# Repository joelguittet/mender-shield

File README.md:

# mender-shield

The Mender Shield illustrates the capability to run a Mender client on heterogeneous platforms such as RaspberryPi (Linux based) and MCUs (RTOS/bare metal).

The following picture shows the Mender devices in the field with the mender-shield on the front, RaspberryPi and ESP32 platforms in the back:
- The Mender logo is displayed on the front of the shield, with an animation of the purple LEDs when an artifact is being downloaded.
- The background color indicates the connectivity status (blue is connected, green is idle, red in case of error).

The following picture shows both sides of the mender-shield:
- The RaspberryPi side has KTD2061 and KTD2058 LEDs drivers from [Kinetic technologies](https://www.kinet-ic.com/ktd2061) driving the 18 RGB LEDs (9 for each side of the PCB) and the [HAT ID EEPROM](https://datasheets.raspberrypi.com/hat/hat-plus-specification.pdf).
- The Arduino side has [ATECC608B](https://www.microchip.com/en-us/product/atecc608b) secure element used to authenticate the device and user EEPROM intented to store [Zephyr LLEXT](https://docs.zephyrproject.org/latest/services/llext/index.html) binary so that the shield also embeds the firmware used to control the display!

[Mender MCU client](https://github.com/joelguittet/mender-mcu-client) is an open source over-the-air (OTA) library updater for MCU devices. Check-out the source and demonstration examples!

## Hardware

The project has been created with [Kicad](https://www.kicad.org/), you can browse the project on [KiCanvas](https://kicanvas.org/?github=https%3A%2F%2Fgithub.com%2Fjoelguittet%2Fmender-shield%2Ftree%2Fmaster%2Fhardware). Gerber files used to manufacture the board are provided.

## Software

The software supports includes a script to perform a very simple demonstration on Raspberry Pi 3 device and an ESP-IDF based application used with the [Wemos D1 r32](.github/docs/Wemos-D1-R32.pdf) ESP32-based evaluation board.

## License

Copyright joelguittet and mender-mcu-client contributors

Licensed under the Apache License, Version 2.0 (the "License");
you may not use this file except in compliance with the License.
You may obtain a copy of the License at

    http://www.apache.org/licenses/LICENSE-2.0

Unless required by applicable law or agreed to in writing, software
distributed under the License is distributed on an "AS IS" BASIS,
WITHOUT WARRANTIES OR CONDITIONS OF ANY KIND, either express or implied.
See the License for the specific language governing permissions and
limitations under the License.

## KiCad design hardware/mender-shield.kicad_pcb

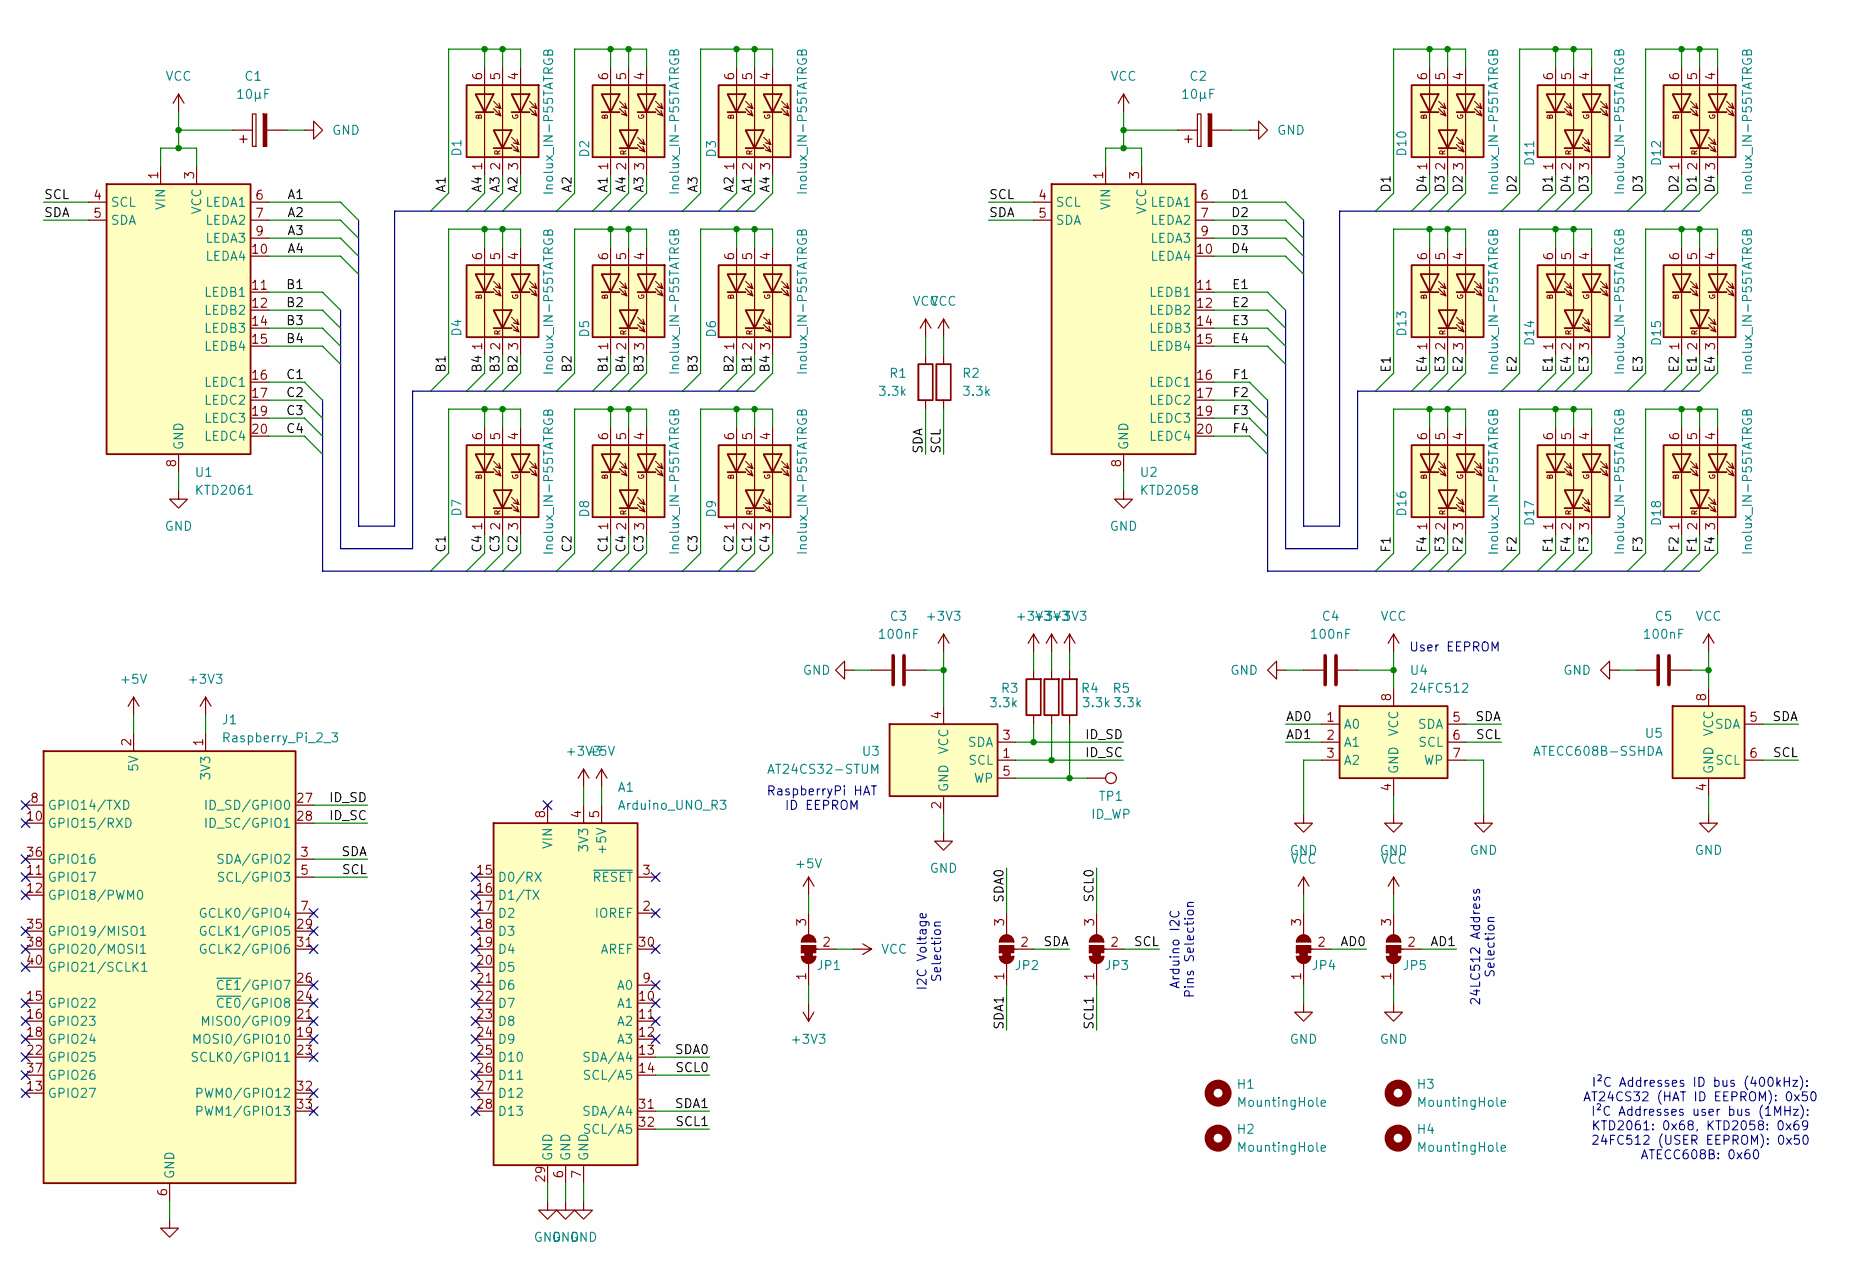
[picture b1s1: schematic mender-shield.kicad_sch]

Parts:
A1: Arduino_UNO_R3
C1, C2: 10µF; C_0805_2012Metric
C3, C4, C5: 100nF; C_0805_2012Metric
D1, D2, D3, D4, D5, D6, D7, D8, D9, D10, D11, D12, D13, D14, D15, D16, D17, D18: Inolux_IN-P55TATRGB; LED_Inolux_IN-P55TATRGB_PLCC6_5.0x5.5mm_P1.8mm
H1, H2, H3, H4: MountingHole; MountingHole_2.7mm_M2.5_DIN965
J1: Raspberry_Pi_2_3; PinSocket_2x20_P2.54mm_Vertical
JP1, JP2, JP3, JP4, JP5: SolderJumper_3_Bridged12; SolderJumper-3_P1.3mm_Bridged12_RoundedPad1.0x1.5mm_NumberL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
R1, R2, R3, R4, R5: 3.3k; R_0805_2012Metric
TP1: ID_WP; TestPoint_Pad_D1.5mm
U1: KTD2061; UQFN-20-1EP_3x3mm_P0.4mm_EP1.7x1.7mm_ThermalVias
U2: KTD2058; UQFN-20-1EP_3x3mm_P0.4mm_EP1.7x1.7mm_ThermalVias
U3: AT24CS32-STUM; SOT-23-5
U4: 24FC512; SOIC-8_3.9x4.9mm_P1.27mm
U5: ATECC608B-SSHDA; SOIC-8_3.9x4.9mm_P1.27mm

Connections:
+3V3: A1.4 (3V3), C3.2, J1.1 (3V3), J1.17 (3V3), JP1.1 (A), R3.2, R4.2, R5.2, U3.4 (VCC)
+5V: A1.5 (+5V), J1.2 (5V), J1.4 (5V), JP1.3 (B)
/A1: D1.4 (AG), D1.5 (AR), D1.6 (AB), D2.1 (KB), D3.2 (KR), U1.6 (LEDA1)
/A2: D1.3 (KG), D2.4 (AG), D2.5 (AR), D2.6 (AB), D3.1 (KB), U1.7 (LEDA2)
/A3: D1.2 (KR), D2.3 (KG), D3.4 (AG), D3.5 (AR), D3.6 (AB), U1.9 (LEDA3)
/A4: D1.1 (KB), D2.2 (KR), D3.3 (KG), U1.10 (LEDA4)
/AD0: JP4.2 (C), U4.1 (A0)
/AD1: JP5.2 (C), U4.2 (A1)
/B1: D4.4 (AG), D4.5 (AR), D4.6 (AB), D5.1 (KB), D6.2 (KR), U1.11 (LEDB1)
/B2: D4.3 (KG), D5.4 (AG), D5.5 (AR), D5.6 (AB), D6.1 (KB), U1.12 (LEDB2)
/B3: D4.2 (KR), D5.3 (KG), D6.4 (AG), D6.5 (AR), D6.6 (AB), U1.14 (LEDB3)
/B4: D4.1 (KB), D5.2 (KR), D6.3 (KG), U1.15 (LEDB4)
/C1: D7.4 (AG), D7.5 (AR), D7.6 (AB), D8.1 (KB), D9.2 (KR), U1.16 (LEDC1)
/C2: D7.3 (KG), D8.4 (AG), D8.5 (AR), D8.6 (AB), D9.1 (KB), U1.17 (LEDC2)
/C3: D7.2 (KR), D8.3 (KG), D9.4 (AG), D9.5 (AR), D9.6 (AB), U1.19 (LEDC3)
/C4: D7.1 (KB), D8.2 (KR), D9.3 (KG), U1.20 (LEDC4)
/D1: D10.4 (AG), D10.5 (AR), D10.6 (AB), D11.1 (KB), D12.2 (KR), U2.6 (LEDA1)
/D2: D10.3 (KG), D11.4 (AG), D11.5 (AR), D11.6 (AB), D12.1 (KB), U2.7 (LEDA2)
/D3: D10.2 (KR), D11.3 (KG), D12.4 (AG), D12.5 (AR), D12.6 (AB), U2.9 (LEDA3)
/D4: D10.1 (KB), D11.2 (KR), D12.3 (KG), U2.10 (LEDA4)
/E1: D13.4 (AG), D13.5 (AR), D13.6 (AB), D14.1 (KB), D15.2 (KR), U2.11 (LEDB1)
/E2: D13.3 (KG), D14.4 (AG), D14.5 (AR), D14.6 (AB), D15.1 (KB), U2.12 (LEDB2)
/E3: D13.2 (KR), D14.3 (KG), D15.4 (AG), D15.5 (AR), D15.6 (AB), U2.14 (LEDB3)
/E4: D13.1 (KB), D14.2 (KR), D15.3 (KG), U2.15 (LEDB4)
/F1: D16.4 (AG), D16.5 (AR), D16.6 (AB), D17.1 (KB), D18.2 (KR), U2.16 (LEDC1)
/F2: D16.3 (KG), D17.4 (AG), D17.5 (AR), D17.6 (AB), D18.1 (KB), U2.17 (LEDC2)
/F3: D16.2 (KR), D17.3 (KG), D18.4 (AG), D18.5 (AR), D18.6 (AB), U2.19 (LEDC3)
/F4: D16.1 (KB), D17.2 (KR), D18.3 (KG), U2.20 (LEDC4)
/ID_SC: J1.28 (ID_SC/GPIO1), R4.1, U3.1 (SCL)
/ID_SD: J1.27 (ID_SD/GPIO0), R3.1, U3.3 (SDA)
/SCL: J1.5 (SCL/GPIO3), JP3.2 (C), R2.2, U1.4 (SCL), U2.4 (SCL), U4.6 (SCL), U5.6 (SCL)
/SCL0: A1.14 (SCL/A5), JP3.3 (B)
/SCL1: A1.32 (SCL/A5), JP3.1 (A)
/SDA: J1.3 (SDA/GPIO2), JP2.2 (C), R1.2, U1.5 (SDA), U2.5 (SDA), U4.5 (SDA), U5.5 (SDA)
/SDA0: A1.13 (SDA/A4), JP2.3 (B)
/SDA1: A1.31 (SDA/A4), JP2.1 (A)
GND: A1.6 (GND), A1.7 (GND), A1.29 (GND), C1.2, C2.2, C3.1, C4.1, C5.1, J1.6 (GND), J1.9 (GND), J1.14 (GND), J1.20 (GND), J1.25 (GND), J1.30 (GND), J1.34 (GND), J1.39 (GND), JP4.1 (A), JP5.1 (A), U1.8 (GND), U1.13 (GND), U1.18 (GND), U1.21 (GND), U2.8 (GND), U2.13 (GND), U2.18 (GND), U2.21 (GND), U3.2 (GND), U4.3 (A2), U4.4 (GND), U4.7 (WP), U5.4 (GND)
unnamed: R5.1, TP1.1, U3.5 (WP)
VCC: C1.1, C2.1, C4.2, C5.2, JP1.2 (C), JP4.3 (B), JP5.3 (B), R1.1, R2.1, U1.1 (VIN), U1.2 (VIN), U1.3 (VCC), U2.1 (VIN), U2.2 (VIN), U2.3 (VCC), U4.8 (VCC), U5.8 (VCC)

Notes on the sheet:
RaspberryPi HAT ID EEPROM
Arduino I2C Pins Selection
I²C Addresses ID bus (400kHz): AT24CS32 (HAT ID EEPROM): 0x50 I²C Addresses user bus (1MHz): KTD2061: 0x68, KTD2058: 0x69 24FC512 (USER EEPROM): 0x50 ATECC608B: 0x60
User EEPROM
24LC512 Address Selection
I2C Voltage Selection

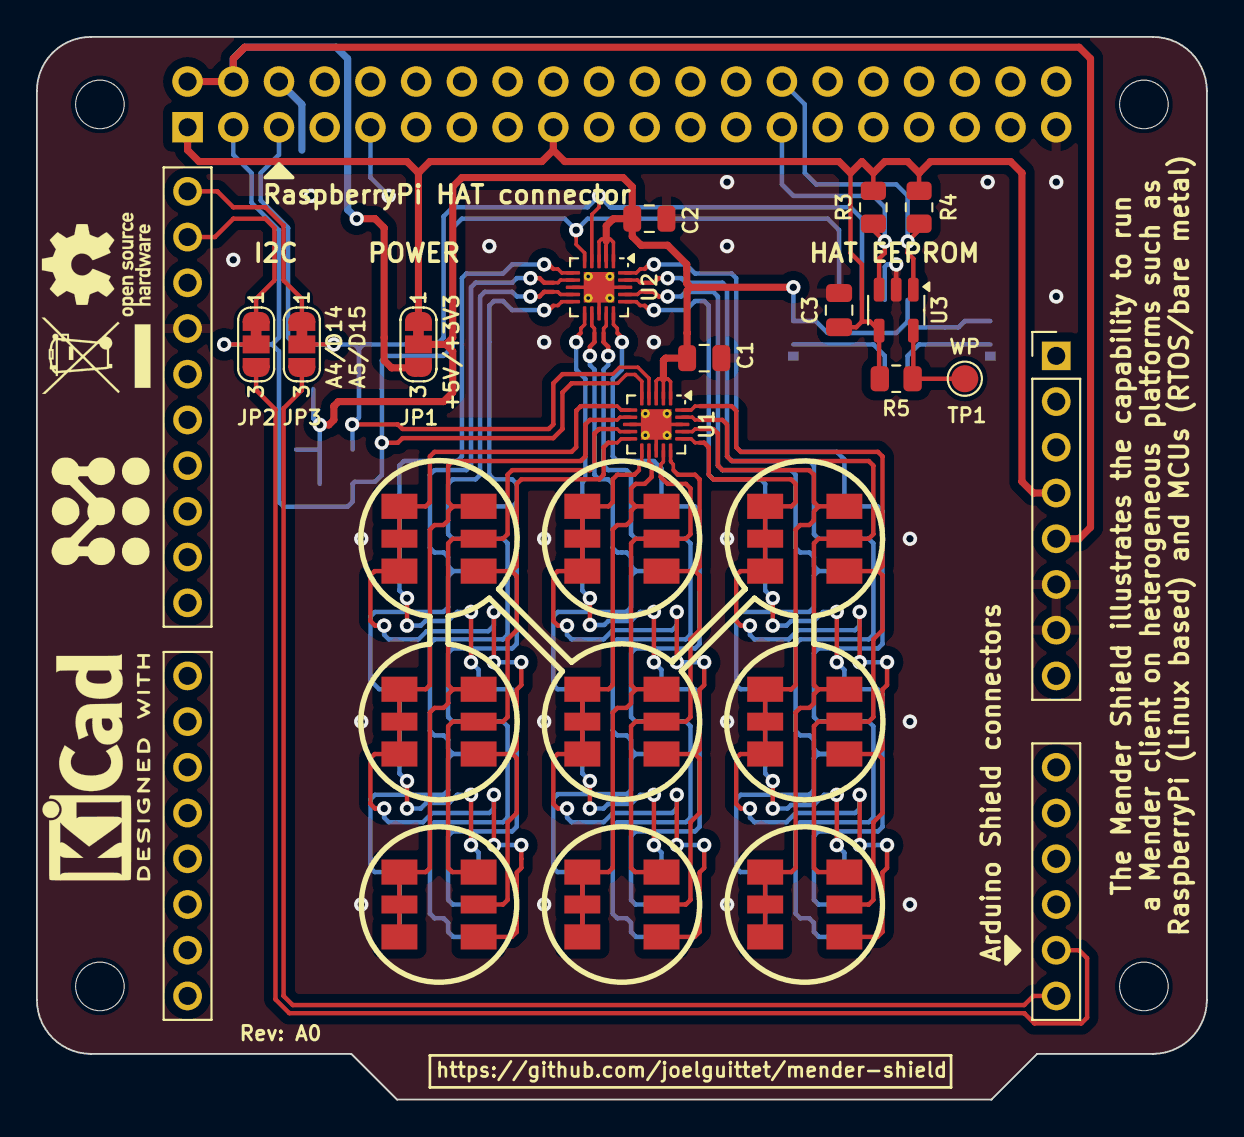
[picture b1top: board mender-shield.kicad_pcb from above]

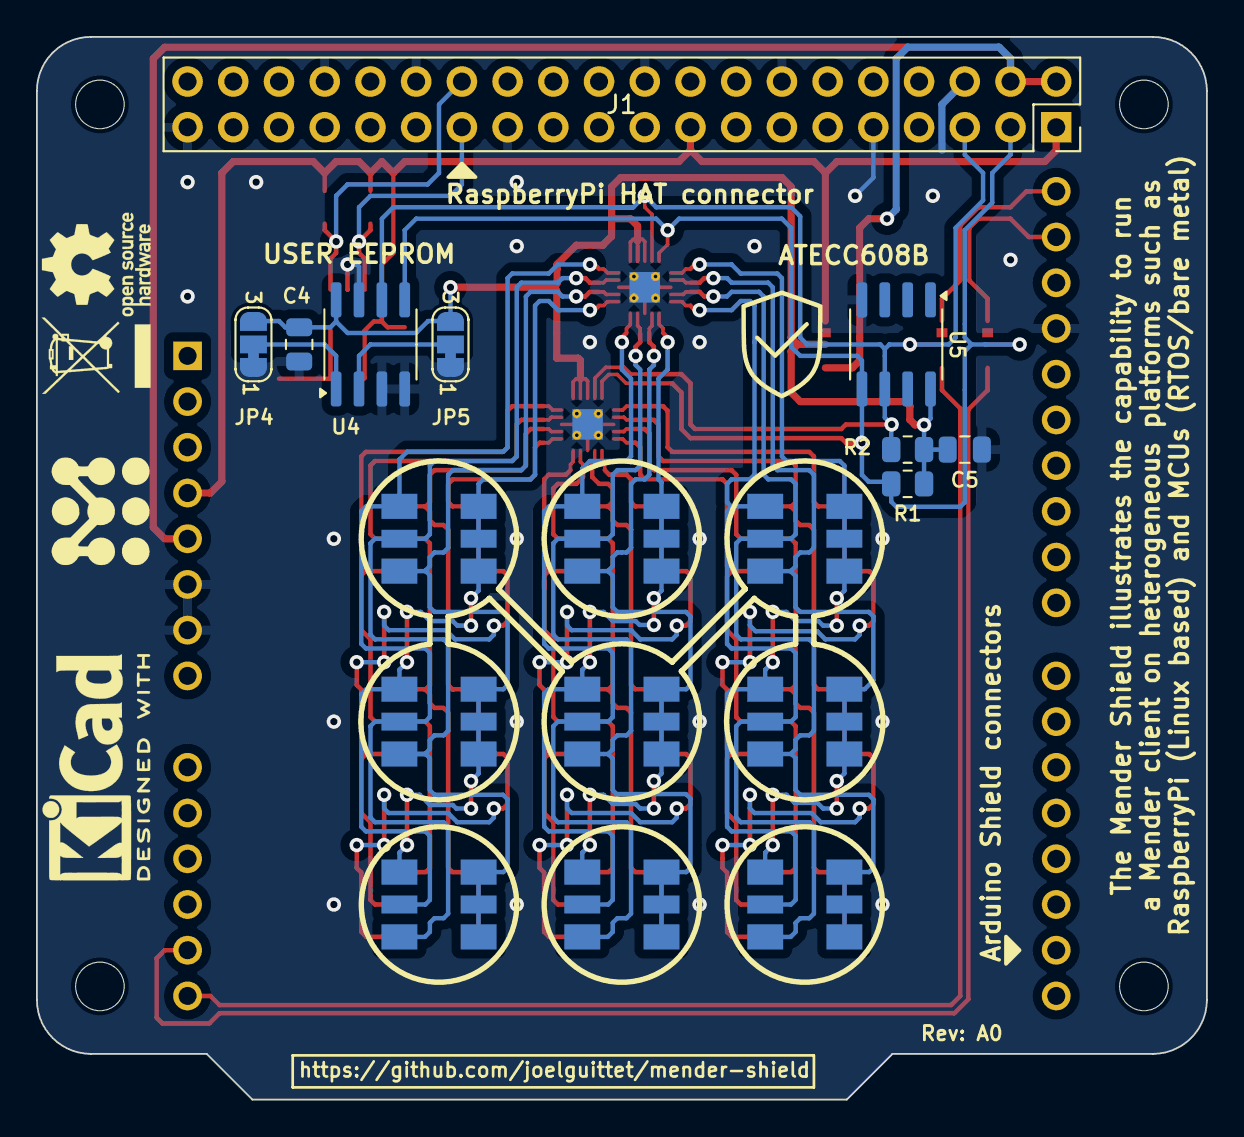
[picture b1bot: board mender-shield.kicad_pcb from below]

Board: 2 copper layers, 65.0 x 59.0 mm, 46 parts (19 on the bottom side), 39 nets.

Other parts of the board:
ATECC608B: LOGO; Trust-Logo_6x6mm_SilkScreen

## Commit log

2024-07-19 Initial release
2025-03-06 software: add raspberrypi3 demonstration script
2025-03-19 github: add ci workflow
2025-03-19 software: add esp-idf firmware
2025-12-04 workflows: update sonarcloud integration
